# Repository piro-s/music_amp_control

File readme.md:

# Music amplifier:  
The amplifier on TDA7851L has two input sources, an additional subwoofer output and a control board for more convenient control.  
With remote controller via shielded Ethernet cable. The control device allows you to switch between two input sources, turn on / off the amplifier (standby-mode) and turn on / off the light music (two-channel mixer with a 1 kHz band-pass filter).

---
## Music amplifier:  
### Scheme:  
[pdf](music_amplifier/docs/music_amplifier_v3.2.pdf)  

### Gerber:  
Archive for production:  
[gerber_3.2](https://github.com/piro-s/music_amp_control/raw/main/music_amplifier/gerber/music_amplifier_v3.2.zip)  

---
## Music control:  
### View:  

### Scheme:  
[pdf](music_control/docs/music_control_v0.2.pdf)  

### Gerber:  
Archive for production:  
[gerber_0.2](https://github.com/piro-s/music_amp_control/raw/main/music_control/gerber/music_control_v0.2.zip)

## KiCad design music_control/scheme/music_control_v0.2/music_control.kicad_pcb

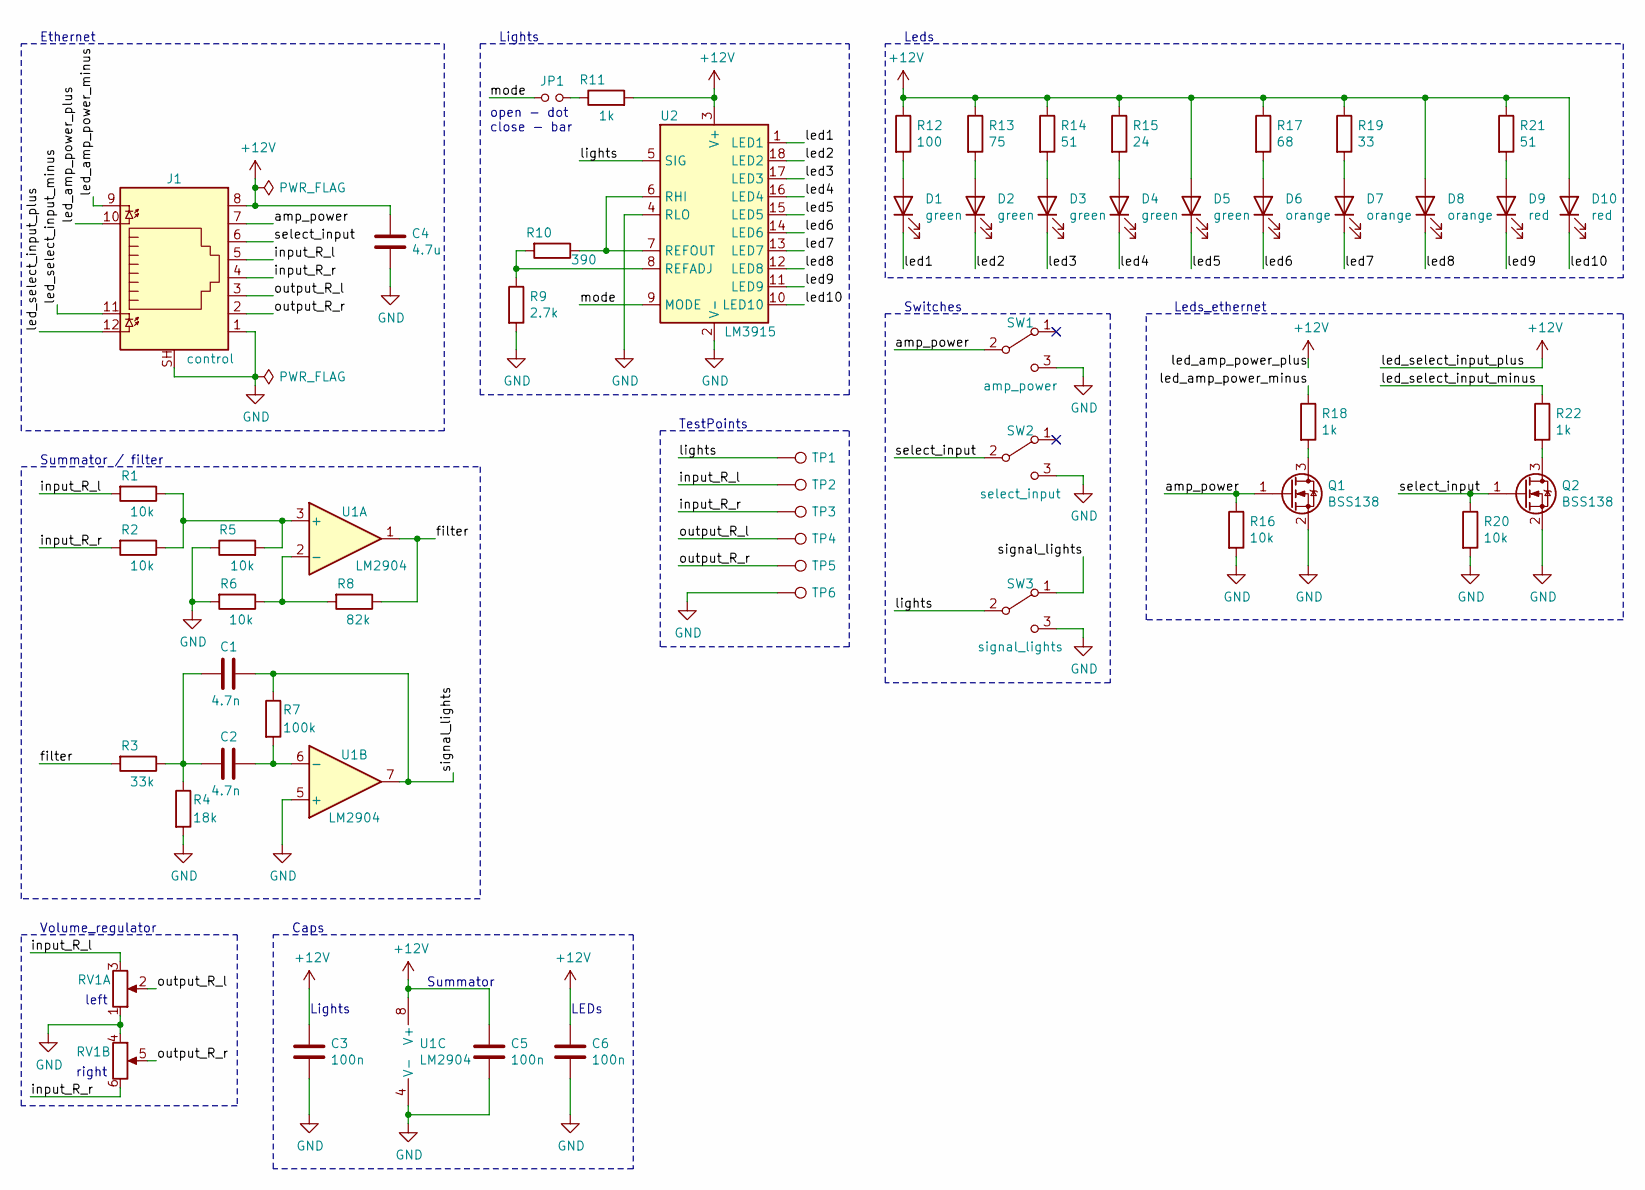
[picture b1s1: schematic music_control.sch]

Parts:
C1, C2: 4.7n; C_0603_1608Metric_Pad1.08x0.95mm_HandSolder
C3, C5, C6: 100n; C_0603_1608Metric_Pad1.08x0.95mm_HandSolder
C4: 4.7u; C_1206_3216Metric_Pad1.33x1.80mm_HandSolder
D1, D2, D3, D4, D5: green; LED_0805_2012Metric_Pad1.15x1.40mm_HandSolder
D6, D7, D8: orange; LED_0805_2012Metric_Pad1.15x1.40mm_HandSolder
D9, D10: red; LED_0805_2012Metric_Pad1.15x1.40mm_HandSolder
J1: control; RJ45_Amphenol_RJHSE538X
JP1: mode; PinHeader_1x02_P2.54mm_Vertical
Q1, Q2: BSS138; SOT-23
R1, R2, R5, R6, R16, R20: 10k; R_0603_1608Metric_Pad0.98x0.95mm_HandSolder
R3: 33k; R_0603_1608Metric_Pad0.98x0.95mm_HandSolder
R4: 18k; R_0603_1608Metric_Pad0.98x0.95mm_HandSolder
R7: 100k; R_0603_1608Metric_Pad0.98x0.95mm_HandSolder
R8: 82k; R_0603_1608Metric_Pad0.98x0.95mm_HandSolder
R9: 2.7k; R_0603_1608Metric_Pad0.98x0.95mm_HandSolder
R10: 390; R_0603_1608Metric_Pad0.98x0.95mm_HandSolder
R11, R18, R22: 1k; R_0603_1608Metric_Pad0.98x0.95mm_HandSolder
R12: 100; R_0603_1608Metric_Pad0.98x0.95mm_HandSolder
R13: 75; R_0603_1608Metric_Pad0.98x0.95mm_HandSolder
R14, R21: 51; R_0603_1608Metric_Pad0.98x0.95mm_HandSolder
R15: 24; R_0603_1608Metric_Pad0.98x0.95mm_HandSolder
R17: 68; R_0603_1608Metric_Pad0.98x0.95mm_HandSolder
R19: 33; R_0603_1608Metric_Pad0.98x0.95mm_HandSolder
RV1: right; Potentiometer_Dual
SW1: amp_power; SW_CuK_OS102011MA1QN1_SPDT_Angled
SW2: select_input; SW_CuK_OS102011MA1QN1_SPDT_Angled
SW3: signal_lights; SW_CuK_OS102011MA1QN1_SPDT_Angled
TP1: lights; TestPoint_Loop_D2.54mm_Drill1.5mm_Beaded
TP2: input_R_l; TestPoint_Loop_D2.54mm_Drill1.5mm_Beaded
TP3: input_R_r; TestPoint_Loop_D2.54mm_Drill1.5mm_Beaded
TP4: output_R_l; TestPoint_Loop_D2.54mm_Drill1.5mm_Beaded
TP5: output_R_r; TestPoint_Loop_D2.54mm_Drill1.5mm_Beaded
TP6: GND; TestPoint_Loop_D2.54mm_Drill1.5mm_Beaded
U1: LM2904; SO-8_3.9x4.9mm_P1.27mm
U2: LM3915; DIP-18_W7.62mm_LongPads

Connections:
+12V: C3.1, C4.1, C5.1, C6.1, D5.2 (A), D8.2 (A), D10.2 (A), J1.8, J1.10, J1.12, R11.2, R12.1, R13.1, R14.1, R15.1, R17.1, R19.1, R21.1, U1.8 (V+), U2.3 (V+)
/amp_power: J1.7, Q1.1 (G), R16.1, SW1.2 (B)
/filter: R3.2, R8.1, U1.1
/input_R_l: J1.5, R1.2, RV1.3, TP2.1; also elsewhere on the board
/input_R_r: J1.4, R2.2, RV1.6, TP3.1; also elsewhere on the board
/led1: D1.1 (K), U2.1 (LED1)
/led2: D2.1 (K), U2.18 (LED2)
/led3: D3.1 (K), U2.17 (LED3)
/led4: D4.1 (K), U2.16 (LED4)
/led5: D5.1 (K), U2.15 (LED5)
/led6: D6.1 (K), U2.14 (LED6)
/led7: D7.1 (K), U2.13 (LED7)
/led8: D8.1 (K), U2.12 (LED8)
/led9: D9.1 (K), U2.11 (LED9)
/led10: D10.1 (K), U2.10 (LED10)
/led_amp_power_minus: J1.9, R18.1
/led_select_input_minus: J1.11, R22.1
/lights: SW3.2 (B), TP1.1, U2.5 (SIG)
/mode: JP1.1, U2.9 (MODE)
/output_R_l: J1.3, RV1.2, TP4.1; also elsewhere on the board
/output_R_r: J1.2, RV1.5, TP5.1; also elsewhere on the board
/select_input: J1.6, Q2.1 (G), R20.1, SW2.2 (B)
/signal_lights: C1.1, R7.1, SW3.1 (A), U1.7
GND: C3.2, C4.2, C5.2, C6.2, J1.1, J1.SH, Q1.2 (S), Q2.2 (S), R4.2, R5.1, R6.2, R9.2, R16.2, R20.2, RV1.1, RV1.4, SW1.3 (C), SW2.3 (C), SW3.3 (C), TP6.1, U1.4 (V-), U1.5 (+), U2.2 (V-), U2.4 (RLO); also elsewhere on the board
unnamed: C1.2, C2.2, R3.1, R4.1
unnamed: C2.1, R7.2, U1.6 (-)
unnamed: D1.2 (A), R12.2
unnamed: D2.2 (A), R13.2
unnamed: D3.2 (A), R14.2
unnamed: D4.2 (A), R15.2
unnamed: D6.2 (A), R17.2
unnamed: D7.2 (A), R19.2
unnamed: D9.2 (A), R21.2
unnamed: JP1.2, R11.1
unnamed: Q1.3 (D), R18.2
unnamed: Q2.3 (D), R22.2
unnamed: R1.1, R2.1, R5.2, U1.3 (+)
unnamed: R6.1, R8.2, U1.2 (-)
unnamed: R10.1, U2.6 (RHI), U2.7 (REFOUT)
unnamed: R9.1, R10.2, U2.8 (REFADJ)

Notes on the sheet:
Summator / filter
Volume_regulator
Ethernet
Leds_ethernet
Leds
Switches
Caps
Summator
Lights
open - dot close - bar
left
right
TestPoints
LEDs

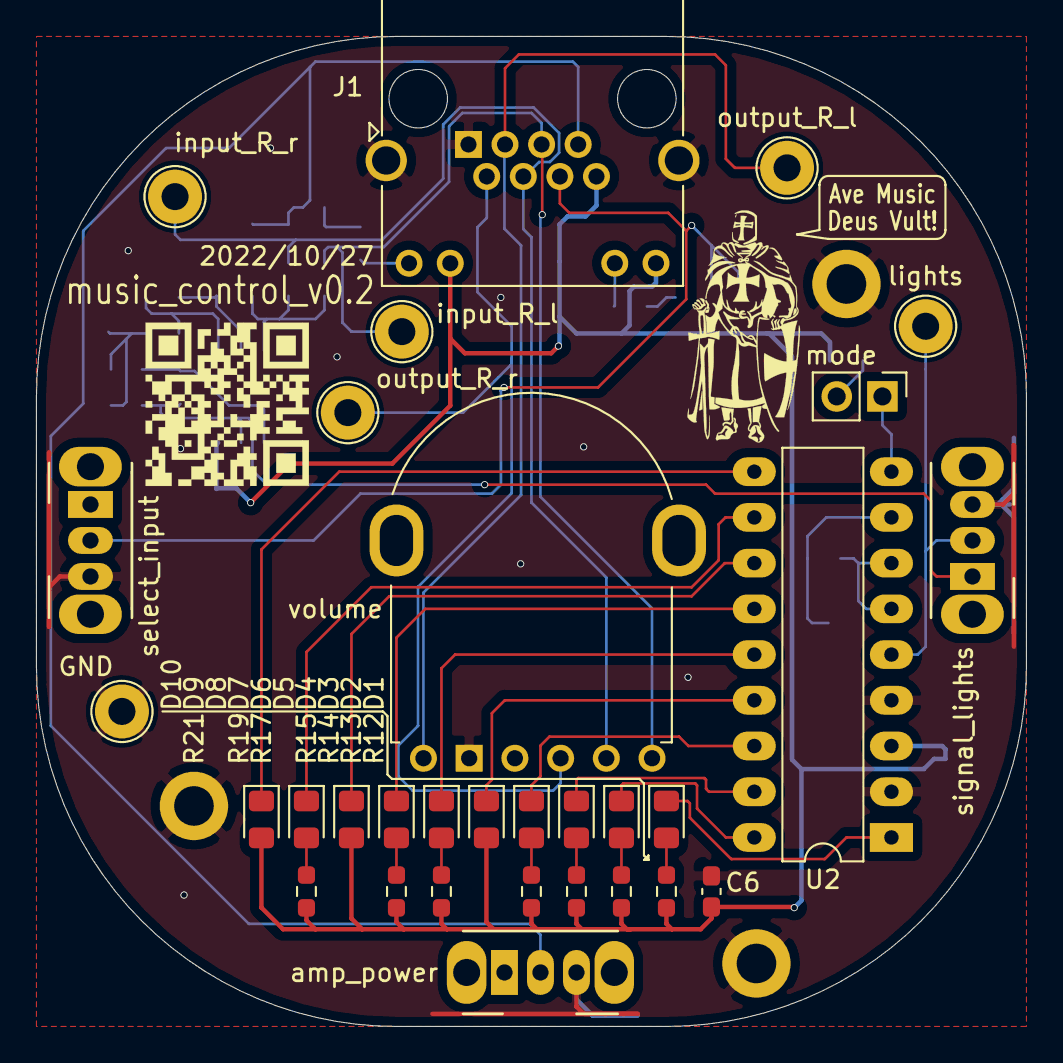
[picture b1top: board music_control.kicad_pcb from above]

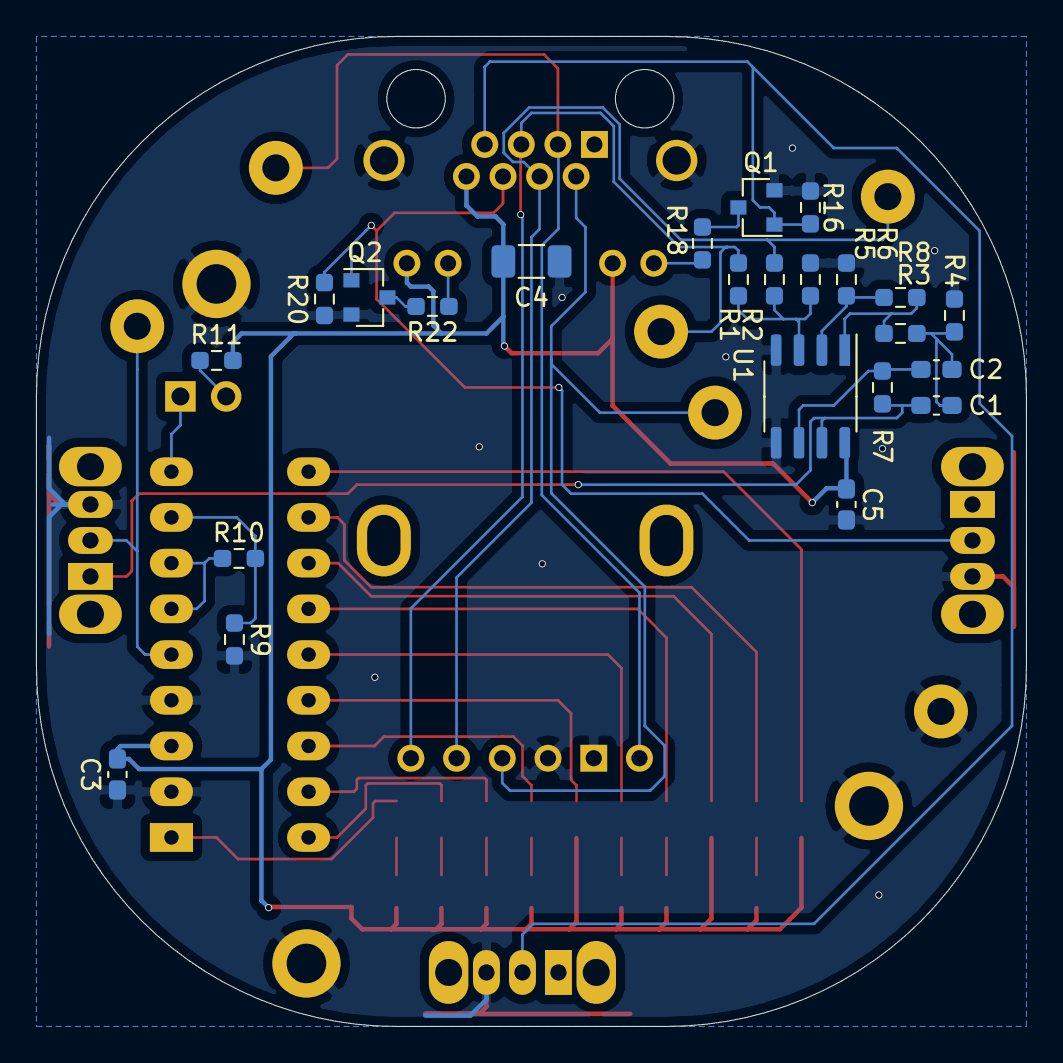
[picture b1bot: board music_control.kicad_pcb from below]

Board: 2 copper layers, 55.0 x 55.0 mm, 54 parts (23 on the bottom side), 40 nets.

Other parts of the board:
volume: right; Potentiometer_Dual

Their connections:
/input_R_l: volume.3; also elsewhere on the board
/input_R_r: volume.6; also elsewhere on the board
/output_R_l: volume.2; also elsewhere on the board
/output_R_r: volume.5; also elsewhere on the board
GND: volume.1, volume.4; also elsewhere on the board

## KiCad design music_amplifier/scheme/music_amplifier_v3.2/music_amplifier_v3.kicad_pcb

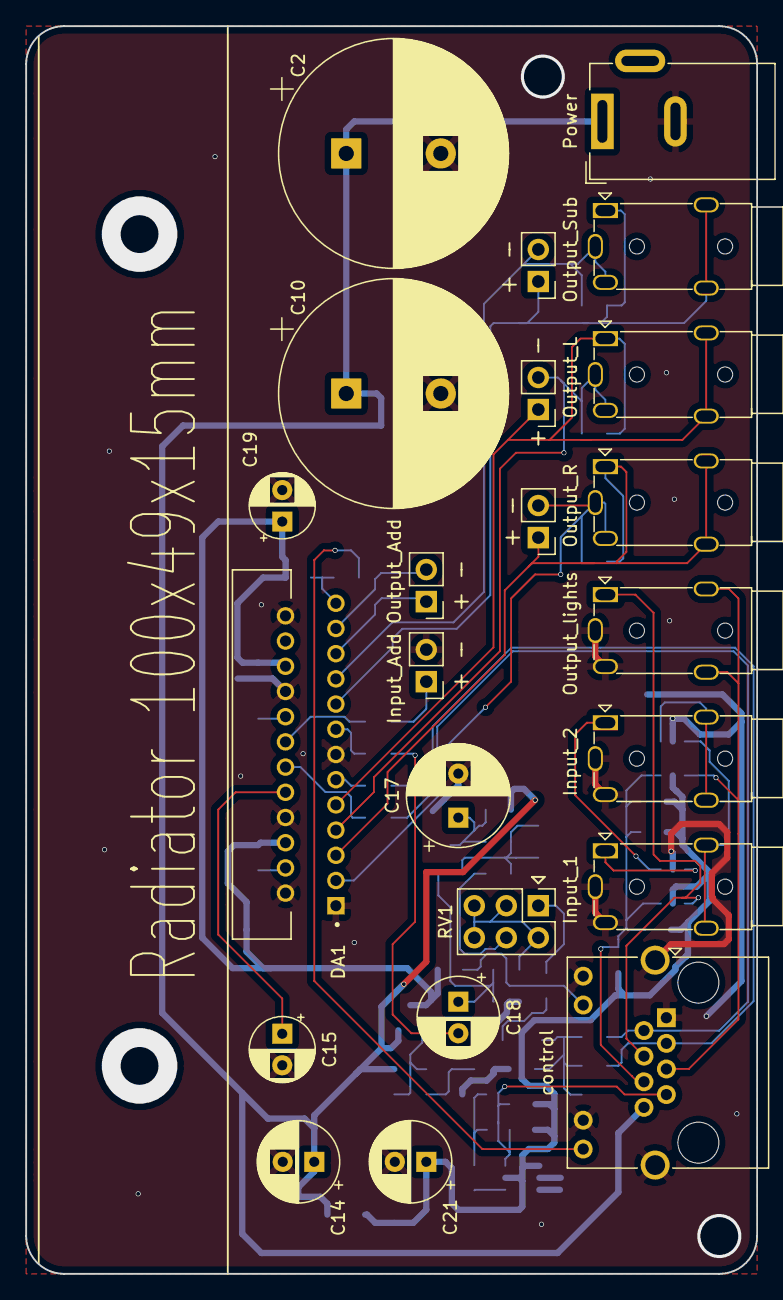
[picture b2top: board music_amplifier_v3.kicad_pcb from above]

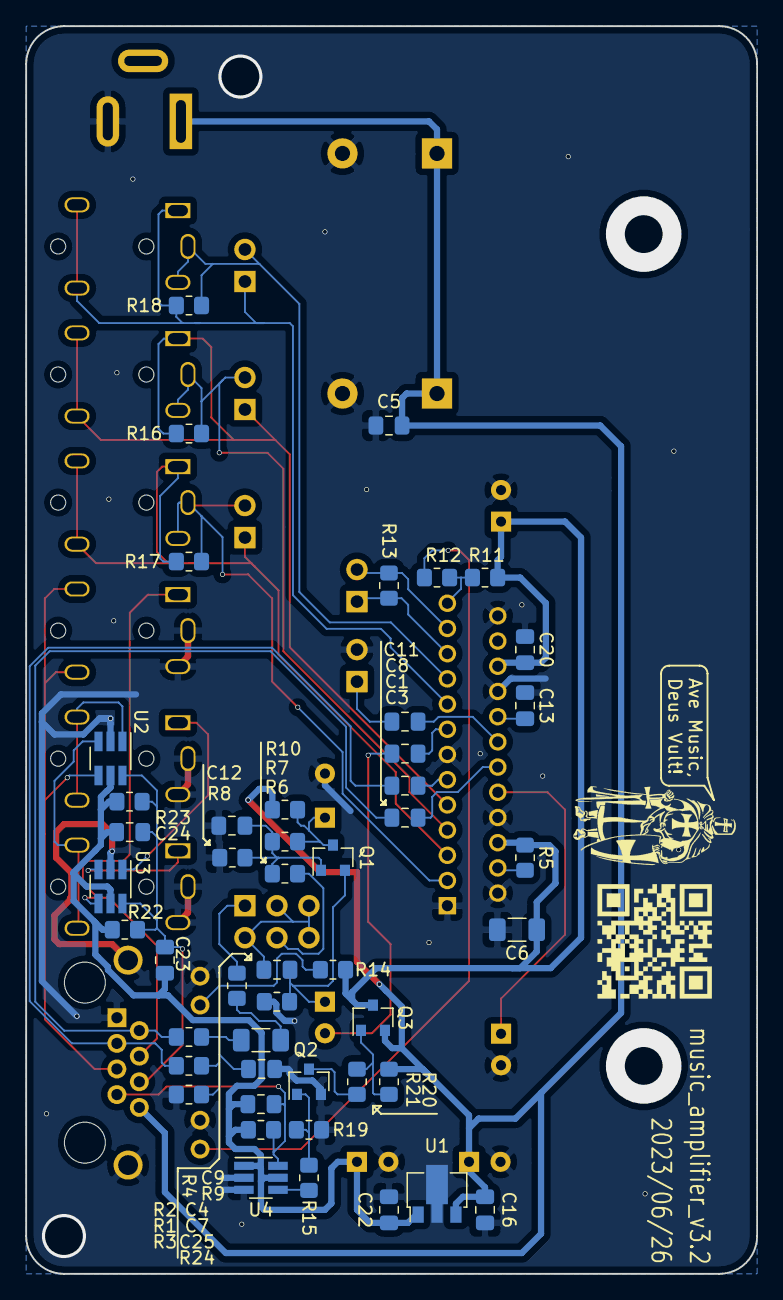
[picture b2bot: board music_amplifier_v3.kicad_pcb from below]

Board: 2 copper layers, 58.0 x 99.0 mm, 71 parts (48 on the bottom side), 46 nets.

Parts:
C1, C3, C5, C7, C8, C11, C16, C20, C22, C23, C24, C25: 100n; C_0805_2012Metric_Pad1.18x1.45mm_HandSolder
C2, C10: 4700u; CP_Radial_D18.0mm_P7.50mm
C4: 1u; C_1206_3216Metric_Pad1.33x1.80mm_HandSolder
C6: 4.7u; C_1206_3216Metric_Pad1.33x1.80mm_HandSolder
C9: 68n; C_0805_2012Metric_Pad1.18x1.45mm_HandSolder
C12: 33n; C_0805_2012Metric_Pad1.18x1.45mm_HandSolder
C13: 0.47u; C_0805_2012Metric_Pad1.18x1.45mm_HandSolder
C14, C18, C21: 100u; CP_Radial_D6.3mm_P2.50mm
C15, C19: 47u; CP_Radial_D5.0mm_P2.50mm
C17: 470u; CP_Radial_D8.0mm_P3.50mm
DA1: TDA7851L; flexiwatt25
J1: Input_Add; PinHeader_1x02_P2.54mm_Vertical
J2: Power; BarrelJack_Wuerth_6941xx301002
J3: Input_1; Jack_3.5mm_PJ322
J4: Input_2; Jack_3.5mm_PJ322
J5: Output_lights; Jack_3.5mm_PJ322
J6: control; RJ45_Amphenol_RJHSE538X
J7: Output_L; PinHeader_1x02_P2.54mm_Vertical
J8: Output_Add; PinHeader_1x02_P2.54mm_Vertical
J9: Output_R; PinHeader_1x02_P2.54mm_Vertical
J10: Output_Sub; PinHeader_1x02_P2.54mm_Vertical
J11: Output_L; Jack_3.5mm_PJ322
J12: Output_R; Jack_3.5mm_PJ322
J13: Output_Sub; Jack_3.5mm_PJ322
Q1: BC817; SOT-23
Q2: BSS138; SOT-23
Q3: AO3401A; SOT-23
R1, R2, R3, R4, R5, R6, R19, R20, R22, R23: 10k; R_0805_2012Metric_Pad1.20x1.40mm_HandSolder
R7: 200k; R_0805_2012Metric_Pad1.20x1.40mm_HandSolder
R8: 240k; R_0805_2012Metric_Pad1.20x1.40mm_HandSolder
R9: 3.3k; R_0805_2012Metric_Pad1.20x1.40mm_HandSolder
R10: 200; R_0805_2012Metric_Pad1.20x1.40mm_HandSolder
R11: 47k; R_0805_2012Metric_Pad1.20x1.40mm_HandSolder
R12, R14: 1.3k; R_0805_2012Metric_Pad1.20x1.40mm_HandSolder
R13, R16, R17, R18: 1M; R_0805_2012Metric_Pad1.20x1.40mm_HandSolder
R15, R21: 1k; R_0805_2012Metric_Pad1.20x1.40mm_HandSolder
R24: 7.5k; R_0805_2012Metric_Pad1.20x1.40mm_HandSolder
RV1: 100k; PinHeader_2x03_P2.54mm_Vertical
U1: L78L05; SOT-89-3
U2, U3, U4: SN74LVC1G3157; SOT-23-6_Handsoldering

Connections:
+5V: C21.1, C22.2, C23.2, C24.2, C25.2, R22.1, R23.1, R24.1, U1.1, U2.5, U3.5, U4.1, U4.5
+12V: C2.1, C5.2, C10.1, C14.1, C16.2, J2.1, J6.8, Q3.2, R10.1, R20.1, U1.3
/amp_gate: R15.1, U4.4
/amp_power: C25.1, J6.7, R24.2, U4.6
/amp_vdd: C6.1, C19.1, C20.2, DA1.6, DA1.20, Q3.3, R5.1, R11.1, R14.1
/input_1_l: J3.T, U2.3
/input_1_r: J3.R, U3.3
/input_2_l: J4.T, U2.1
/input_2_r: J4.R, U3.1
/input_R_l: J5.T, J6.5, U2.4
/input_R_r: J5.R, J6.4, U3.4
/input_speaker_sub: C8.2, C18.2
/led_cd: J6.12, R12.2
/led_power: J6.10, R14.2
/output_R_l: C1.2, J6.3, R1.2
/output_R_r: C3.2, J6.2, R2.2
/select_input: C23.1, C24.1, J6.6, R22.2, R23.2, U2.6, U3.6
GND: C2.2, C5.1, C6.2, C7.1, C10.2, C12.1, C13.1, C14.2, C15.2, C16.1, C17.2, C19.2, C20.1, C21.2, C22.1, DA1.1, DA1.2, DA1.8, DA1.13, DA1.18, DA1.24, J1.2, J2.2, J3.S, J4.S, J5.S, J6.1, J6.9, J6.11, J6.SH, Q2.2, R3.2, R8.2, R9.2, R19.2, U1.2, U2.2, U3.2, U4.2, U4.3
unnamed: C1.1, DA1.11
unnamed: C3.1, DA1.12
unnamed: C4.1, R4.2
unnamed: C4.2, C7.2, R1.1, R2.1, R3.1
unnamed: C8.1, DA1.15
unnamed: C9.2, RV1.2, RV1.3, RV1.5, RV1.6
unnamed: C11.1, DA1.14
unnamed: C11.2, J1.1
unnamed: C12.2, Q1.1, R6.2, R7.2, R8.1
unnamed: C13.2, DA1.16
unnamed: C15.1, DA1.10
unnamed: C17.1, Q1.3, R7.1, R10.2
unnamed: C9.1, C18.1, Q1.2, R9.1
unnamed: DA1.3, J9.2, J12.S, R17.1
unnamed: DA1.4, R5.2
unnamed: DA1.5, J9.1, J12.R, J12.T, R17.2
unnamed: DA1.7, J7.2, J11.S, R16.1
unnamed: DA1.9, J7.1, J11.R, J11.T, R16.2
unnamed: DA1.17, J10.1, J13.R, J13.T, R18.2
unnamed: DA1.19, J10.2, J13.S, R18.1
unnamed: DA1.21, J8.1, R13.2
unnamed: DA1.23, J8.2, R13.1
unnamed: DA1.25, R11.2, R12.1
unnamed: Q2.1, R15.2, R19.1
unnamed: Q2.3, R21.2
unnamed: Q3.1, R20.2, R21.1
unnamed: R4.1, RV1.1
unnamed: R6.1, RV1.4

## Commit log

2023-07-30 Initial
    Amplifier on TDA7851L with remote control.
